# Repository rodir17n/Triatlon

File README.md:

# 🤖 Juegos Bonaerenses de Robótica

Proyecto web simple en HTML sobre los **Juegos Bonaerenses de Robótica**, pensado para compartir información básica sobre esta competencia educativa y tecnológica.

---

## 📌 Descripción

Este proyecto contiene una página web sencilla desarrollada en **HTML y CSS**, diseñada para presentar:

- Qué son los Juegos Bonaerenses de Robótica.
- Sus objetivos educativos.
- La importancia de la tecnología y la innovación.
- Información básica para estudiantes y escuelas.

---

## 🚀 Tecnologías utilizadas

- HTML5
- CSS3

---

## 📂 Estructura del proyecto

```bash
/
├── index.html
└── README.md

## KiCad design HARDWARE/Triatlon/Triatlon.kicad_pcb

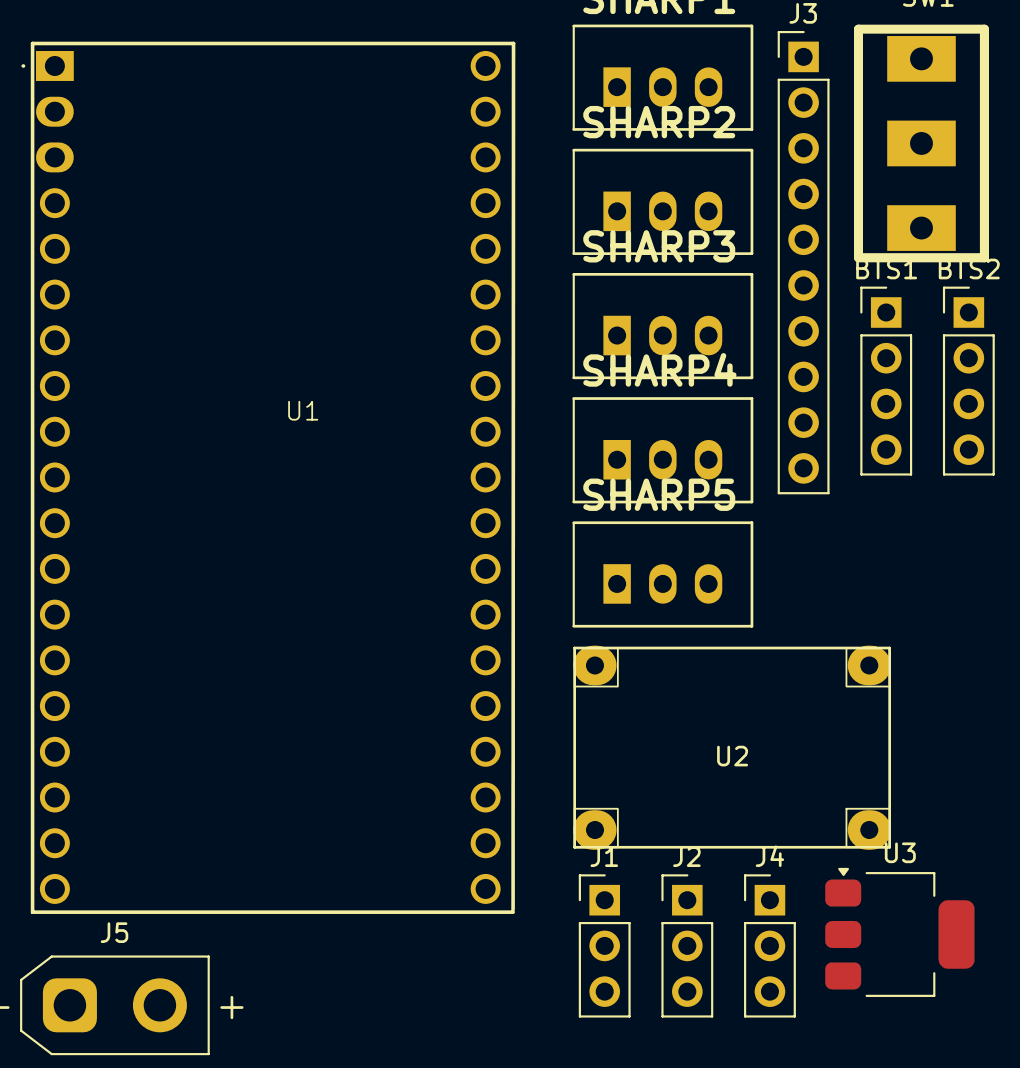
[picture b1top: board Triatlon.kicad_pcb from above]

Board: 2 copper layers, 16 parts (0 on the bottom side), 5 nets, no tracks yet.

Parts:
BTS1, BTS2: Conn_01x04_Pin; PinHeader_1x04_P2.54mm_Vertical
J1: TCRT5000-1; PinHeader_1x03_P2.54mm_Vertical
J2: TCRT5000-2; PinHeader_1x03_P2.54mm_Vertical
J3: Conn_01x10; PinHeader_1x10_P2.54mm_Vertical
J4: TCRT5000-3; PinHeader_1x03_P2.54mm_Vertical
J5: TB_1X2; AMASS_XT30UPB-F_1x02_P5.0mm_Vertical
SHARP1, SHARP2, SHARP3, SHARP4, SHARP5: Conn_01x03; JST-3V
SW1: SW1; SW_SPDT_TH_Vertical
U1: ESP32_DEVKITC; esp32 38 pin usb-c
U2: Mini360; Mini360_step-down
U3: AMS1117-3.3; SOT-223-3_TabPin2

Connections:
+3.3V: J1.3, J2.3, J4.3, U3.2 (VO)
+5V: BTS1.1, BTS2.1, J3.1, SHARP1.3, SHARP2.3, SHARP3.3, SHARP4.3, SHARP5.3, U1.19 (5V), U3.3 (VI)
GND: BTS1.4, BTS2.4, J1.1, J2.1, J3.10, J4.1, J5.2, SHARP1.1, SHARP2.1, SHARP3.1, SHARP4.1, SHARP5.1, U1.14 (GND), U2.1 (IN-), U2.3 (OUT-), U3.1 (GND)
VCC: J5.1, SW1.2 (B)
VCC1: SW1.1 (A), U2.2 (IN+)

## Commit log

2026-04-14 Agrego el proyecto
2026-05-10 Prueba
2026-05-10 Reestablezco el esquematico
2026-05-18 Hice readme prueba
